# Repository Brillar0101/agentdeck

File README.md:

<div align="center">

# AgentDeck

**AgentDeck is an open-source desk macropad for supervising AI coding agents.**

</div>

_AgentDeck is optimized for people running several coding agents at once who
want glanceable status and one-hand control. It is a desk device, not a
portable one: USB-C only, no battery, no radio._

- [Design notes](v1/DESIGN.md)
- [Changelog](CHANGELOG.md)
- [Licensing](LICENSING.md)

Six agent keys light up with each agent's live state (idle, thinking, working,
blocked, done). Press one to focus that session. The command keys accept or
reject work, the dial scrubs and confirms, and the joystick navigates. A host
bridge maps Claude Code hooks to the key colours, so the board answers "which
of my sessions needs me?" without alt-tabbing.

> **This is a Codex Micro-inspired project.** The concept follows OpenAI and
> Work Louder's Codex Micro, and the control layout deliberately echoes it. It
> is an independent build, not affiliated with, endorsed by, or produced with
> OpenAI, Work Louder, or Anthropic. The board, firmware and enclosure are
> original work; no Codex Micro files were used. Some material in this
> repository (vendor footprints, datasheets, reference photographs, third-party
> cap and knob models) is not ours to license. See [LICENSING.md](LICENSING.md).

## Renders

| | |
|---|---|
|  |  |
|  |  |

## Changelog

Hardware revisions are tracked in the [changelog](CHANGELOG.md). Because the
board is text-based KiCad, every fabricated revision maps to a tagged commit,
and a physical board can be traced back to the exact design it was made from.

## Versions

| Version | What it is | Where |
|---|---|---|
| **V1** (this release) | 95 x 95 mm 4-layer RP2040 board, 13 keys, JLCPCB PCBA | `v1/hardware/` |

What comes next (v1.0 bring-up, the v1.1 depth release, and what is
deliberately parked) is in the [roadmap](docs/ROADMAP.md).

## Status

| Part | State |
|---|---|
| Schematic + PCB | Complete. 4 layers, fully routed, 0 DRC errors, 0 ERC errors |
| Firmware | Written (CircuitPython, plus an Arduino/C++ port), untested on hardware |
| Host bridge | Written. Maps Claude Code hooks to agent-key colours |
| Enclosure | Modelled and fit-checked in Blender, STLs exported, not yet printed |
| Fab package | Gerbers, BOM and CPL generated for JLCPCB |

Nothing has been manufactured yet, so none of it is hardware-verified.

## Packages

The repository is organized by discipline. Each directory is self-contained
and has its own README where the workflow needs explaining.

| Directory | Contents |
|---|---|
| `v1/hardware/` | KiCad 10 project: `AgentDeck.kicad_pcb`, `AgentDeck.kicad_sch`, footprint / symbol / 3D libraries |
| `v1/enclosure/` | Blender assembly (`AgentDeck-v2-assembled.blend`), the parametric case generator (`src/generate_case.py`), printable STLs, keycap icon art |
| `v1/firmware/` | CircuitPython firmware (`boot.py`, `code.py`) and the Arduino port |
| `v1/host/` | `agentdeck_bridge.py`, the Claude Code hook bridge |
| `v1/fab/` | Gerbers, drill files, BOM and CPL for JLCPCB |
| `docs/` | design notes, datasheets, reference material, renders in `docs/img/` |
| `LICENSES/` | full licence texts |

## Hardware

The board is a 95 x 95 mm 4-layer PCB, drawn in KiCad 10.

- 13 Kailh Choc hot-swap keys on an 18.7 x 19.3 mm grid, each with a
  reverse-mount SK6812MINI-E RGB LED shining up through the cap
- EC11 rotary encoder (top left) and Alps SKQUCAA010 5-way joystick (top right)
- RP2040 with W25Q128 16 MB flash, USB-C, BOOT button, SWD pads
- Everything is wired directly to GPIO. There is no key matrix, so there is
  no ghosting to debounce around
- All SMD parts sit on the back of the board and hang down into the case
  tray; only the switches, encoder and joystick face up

Keycaps carry simple engraved-style icons (dice for the six agent keys,
thumbs up and down for accept and reject) rendered from
[Lucide](https://lucide.dev) glyphs. The encoder and joystick caps are white.

## Enclosure

Two printed parts plus four printed cover caps. The PCB drops into the bottom
tray component-side down, the lid closes over it, and four screws clamp the
stack into brass inserts.

| Feature | Spec |
|---|---|
| Screws | M2.5 x 8 mm button head (ISO 7380), head 4.7 x 1.3 mm |
| Lid | 5.2 mm counterbore, 2.5 mm deep, over a 2.9 mm shaft hole |
| Inserts | M2.5 brass heat-set, 4.0 mm OD x 5.0 mm, melted into a 3.6 mm boss bore |
| Cover caps | printed 5.0 x 1.2 mm plugs that hide the screw heads |
| Fit | 0.4 mm pocket clearance around the board (a deliberately loose fit) |
| USB | side port through the tray wall, sized for the plug plus a slim overmould |
| Walls | 2.6 mm, with a 0.6 mm bevel on exposed edges |

Print `v1/enclosure/case-bottom.stl`, `v1/enclosure/case-top-lid.stl`, and four of
`v1/enclosure/case-cover-plug.stl`. The case is generated, not sculpted: edit the
parameters in `v1/enclosure/src/generate_case.py` and re-run it to get new STLs.

## Firmware

Copy `v1/firmware/boot.py` and `code.py` onto a CIRCUITPY drive running
CircuitPython 9.x, with `adafruit_hid` and `neopixel` in `lib/`. An Arduino
port with identical behaviour lives in `v1/firmware/arduino/` if you prefer a
compiled build.

The command keys send Ctrl+Alt chords, the dial sets reasoning effort, and the
joystick navigates. `v1/firmware/README.md` has the full control table, colour
legend, pin map, and the three constants to confirm on first hardware.

## Development

- **Board edits**: open `v1/hardware/AgentDeck.kicad_pcb` in KiCad 10. After
  copper changes, refill zones before running DRC, then regenerate `v1/fab/`
  with `kicad-cli`.
- **Case edits**: run `v1/enclosure/src/generate_case.py` in Blender to rebuild
  the STLs from parameters.
- **Renders**: the assembly lives in `v1/enclosure/AgentDeck-v2-assembled.blend`;
  reference renders are committed under `docs/img/`.
- Derived files (board 3D exports, `.dsn`/`.ses` routing intermediates,
  autorouter logs) are gitignored and regenerate from the board.

## Licence

Multi-licensed, as is normal for open hardware. See [LICENSING.md](LICENSING.md).

| What | Licence |
|---|---|
| Software (`v1/firmware/`, `v1/host/`) | [MIT](LICENSES/MIT.txt) |
| Hardware (board, enclosure, fab files) | [CERN-OHL-S v2](LICENSES/CERN-OHL-S-v2.txt) |
| Documentation | [CC-BY-4.0](LICENSES/CC-BY-4.0.txt) |

Vendor footprints, datasheets and reference images keep their original terms.
Keycap icons are from [Lucide](https://lucide.dev) (ISC).

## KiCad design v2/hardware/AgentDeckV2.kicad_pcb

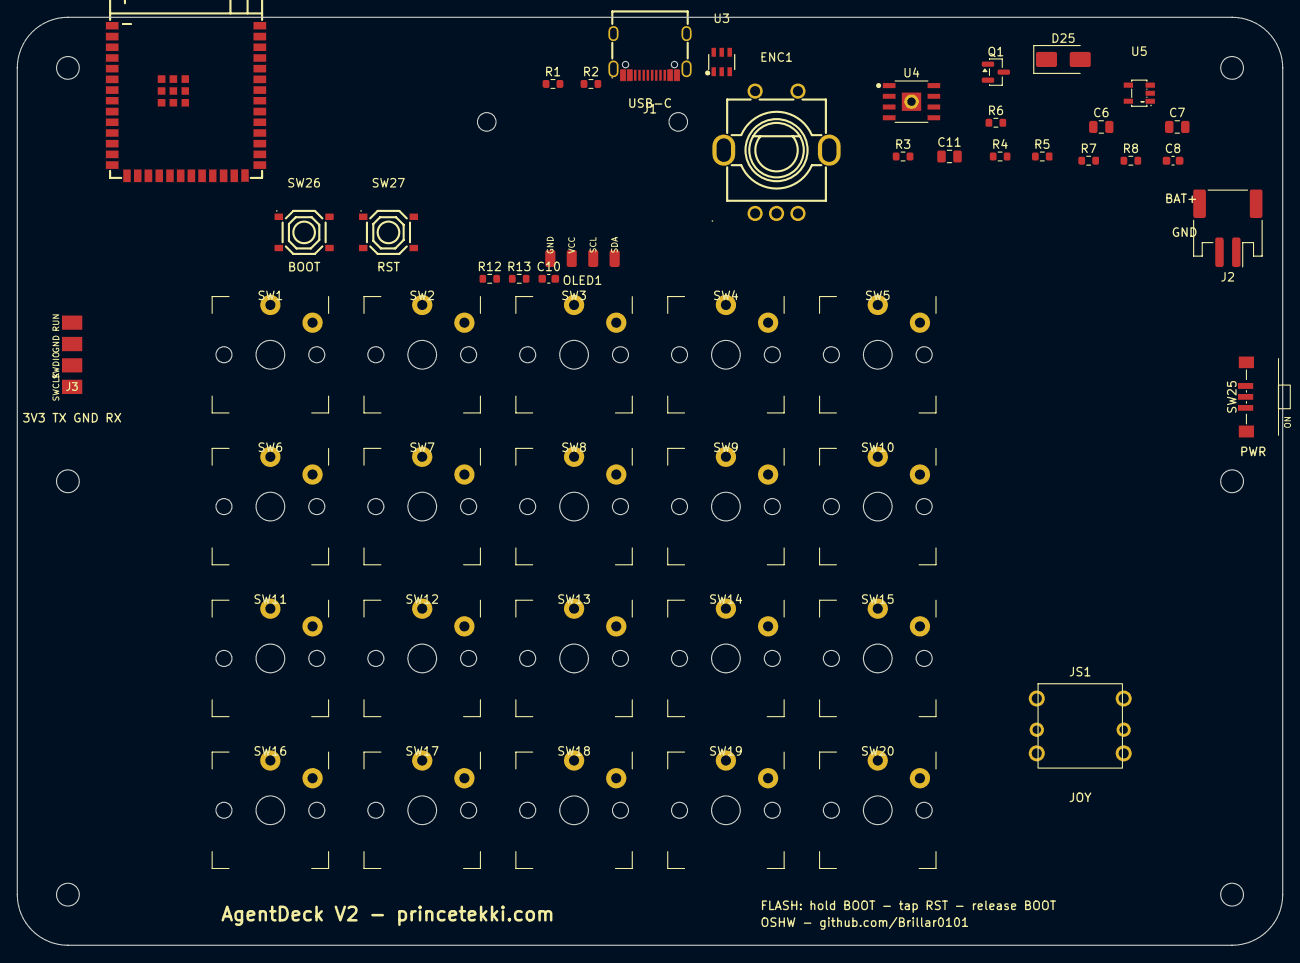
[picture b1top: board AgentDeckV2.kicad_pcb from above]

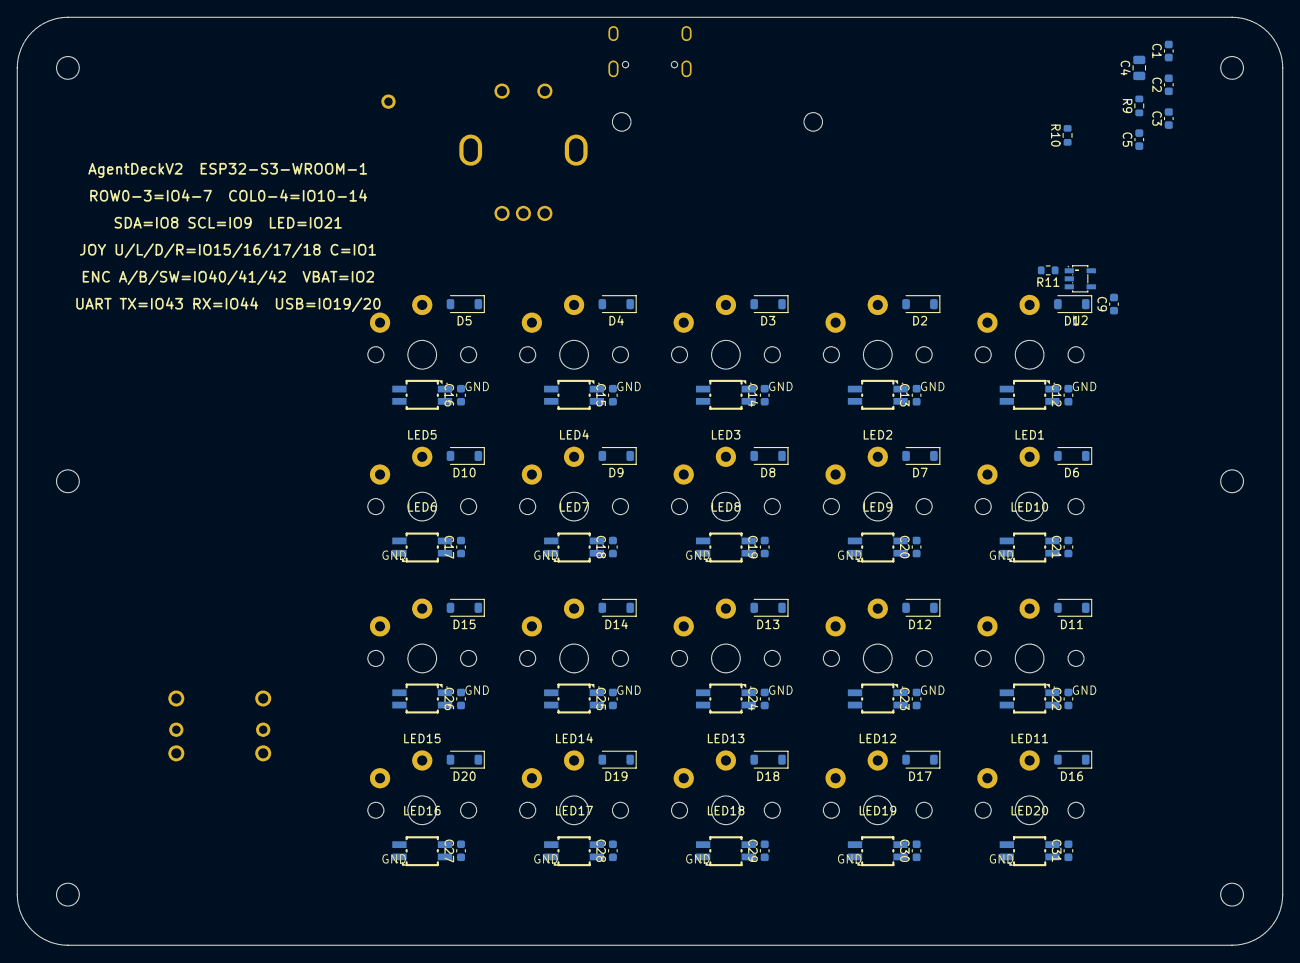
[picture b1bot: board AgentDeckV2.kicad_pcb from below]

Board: 2 copper layers, 150.0 x 110.0 mm, 126 parts (70 on the bottom side), 81 nets, no tracks yet.

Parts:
C1, C2, C3, C5, C8, C9, C10, C12, C13, C14, C15, C16, C17, C18, C19, C20, C21, C22, C23, C24, C25, C26, C27, C28, C29, C30, C31: C_0603_1608Metric
C4, C6, C7, C11: C_0805_2012Metric
D1, D2, D3, D4, D5, D6, D7, D8, D9, D10, D11, D12, D13, D14, D15, D16, D17, D18, D19, D20: D_SOD-123
D25: D_SMA
ENC1: SW-TH_EC11E1820402
J1: USB-C_SMD-TYPE-C-31-M-12_1
J2: JST_PH_S2B-PH-SM4-TB_1x02-1MP_P2.00mm_Horizontal
J3: SWD; ProgPads_1x4
JS1: SKQUCAA010
LED1, LED2, LED3, LED4, LED5, LED6, LED7, LED8, LED9, LED10, LED11, LED12, LED13, LED14, LED15, LED16, LED17, LED18, LED19, LED20: LED-SMD_4P-L3.2-W2.8-LS5.9_SK6812MINI-E
MH1, MH2, MH3, MH4, MH5, MH6: M2.5; MountingHole_M2_5
OLED1: OLED_HS96L03
Q1: SOT-23
R1, R2, R3, R4, R5, R6, R7, R8, R9, R10, R11, R12, R13: R_0603_1608Metric
SW1, SW2, SW3, SW4, SW5, SW6, SW7, SW8, SW9, SW10, SW11, SW12, SW13, SW14, SW15, SW16, SW17, SW18, SW19, SW20: ChocV1_Direct
SW25: MSK12C02
SW26, SW27: SW-SMD_4P-L5.1-W5.1-P3.70-LS6.5-TL_H1.5
U1: WIRELM-SMD_ESP32-S3-WROOM-1
U2, U5: SOT-23-5_L3.0-W1.7-P0.95-LS2.8-BR
U3: SOT-23-6_L2.9-W1.6-P0.95-LS2.8-BL
U4: ESOP-8_TP4056

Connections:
+3V3: C1.1, C2.1, C3.1, C4.1, C7.1, C10.1, J3.1, OLED1.2, R9.1, R10.1, R12.1, R13.1, U1.2, U5.5
BAT+: J2.1, Q1.3, R7.1, U4.5
CC1: J1.A5, R1.1
CC2: J1.B5, R2.1
CHRG: R4.1, U4.7
CHRG_SNS: R4.2, U1.24
COL0: SW1.1, SW6.1, SW11.1, SW16.1, U1.18
COL1: SW2.1, SW7.1, SW12.1, SW17.1, U1.19
COL2: SW3.1, SW8.1, SW13.1, SW18.1, U1.20
COL3: SW4.1, SW9.1, SW14.1, SW19.1, U1.21
COL4: SW5.1, SW10.1, SW15.1, SW20.1, U1.22
EN: C5.1, R9.2, SW27.1, SW27.3, U1.3
ENC_A: ENC1.A, U1.33
ENC_B: ENC1.B, U1.34
ENC_SW: ENC1.D, U1.35
GND: C1.2, C2.2, C3.2, C4.2, C5.2, C6.2, C7.2, C8.2, C9.2, C10.2, C11.2, C12.2, C13.2, C14.2, C15.2, C16.2, C17.2, C18.2, C19.2, C20.2, C21.2, C22.2, C23.2, C24.2, C25.2, C26.2, C27.2, C28.2, C29.2, C30.2, C31.2, ENC1.C, ENC1.E, ENC1.F, ENC1.G, J1.1, J1.2, J1.3, J1.4, J1.A1B12, J1.B1A12, J2.2, J3.3, JS1.4, LED1.1, LED2.1, LED3.1, LED4.1, LED5.1, LED6.1, LED7.1, LED8.1, LED9.1, LED10.1, LED11.1, LED12.1, LED13.1, LED14.1, LED15.1, LED16.1, LED17.1, LED18.1, LED19.1, LED20.1, OLED1.1, R1.2, R2.2, R3.2, R6.2, R8.2, SW26.2, SW26.4, SW27.2, SW27.4, U1.1, U1.40, U1.41, U2.1, U2.3, U3.2, U4.1, U4.3, U5.2
IO0: R10.2, SW26.1, SW26.3, U1.27
JOY_CTR: JS1.6, U1.39
JOY_DOWN: JS1.3, U1.10
JOY_LEFT: JS1.2, U1.9
JOY_RIGHT: JS1.5, U1.11
JOY_UP: JS1.1, U1.8
KD1: D1.2, SW1.2
KD2: D2.2, SW2.2
KD3: D3.2, SW3.2
KD4: D4.2, SW4.2
KD5: D5.2, SW5.2
KD6: D6.2, SW6.2
KD7: D7.2, SW7.2
KD8: D8.2, SW8.2
KD9: D9.2, SW9.2
KD10: D10.2, SW10.2
KD11: D11.2, SW11.2
KD12: D12.2, SW12.2
KD13: D13.2, SW13.2
KD14: D14.2, SW14.2
KD15: D15.2, SW15.2
KD16: D16.2, SW16.2
KD17: D17.2, SW17.2
KD18: D18.2, SW18.2
KD19: D19.2, SW19.2
KD20: D20.2, SW20.2
LED_D1: LED1.2, R11.2
LED_D2: LED1.4, LED2.2
LED_D3: LED2.4, LED3.2
LED_D4: LED3.4, LED4.2
LED_D5: LED4.4, LED5.2
LED_D6: LED5.4, LED6.2
LED_D7: LED6.4, LED7.2
LED_D8: LED7.4, LED8.2
LED_D9: LED8.4, LED9.2
LED_D10: LED9.4, LED10.2
LED_D11: LED10.4, LED11.2
LED_D12: LED11.4, LED12.2
LED_D13: LED12.4, LED13.2
LED_D14: LED13.4, LED14.2
LED_D15: LED14.4, LED15.2
LED_D16: LED15.4, LED16.2
LED_D17: LED16.4, LED17.2
LED_D18: LED17.4, LED18.2
LED_D19: LED18.4, LED19.2
LED_D20: LED19.4, LED20.2
LED_DATA: U1.23, U2.2
LED_DATA_BUF: R11.1, U2.4
PROG: R3.1, U4.2
ROW0: D1.1, D2.1, D3.1, D4.1, D5.1, U1.4
ROW1: D6.1, D7.1, D8.1, D9.1, D10.1, U1.5
ROW2: D11.1, D12.1, D13.1, D14.1, D15.1, U1.6
ROW3: D16.1, D17.1, D18.1, D19.1, D20.1, U1.7
RXD: J3.4, U1.36
SCL: OLED1.3, R13.2, U1.17
SDA: OLED1.4, R12.2, U1.12
STDBY: R5.1, U4.6
STDBY_SNS: R5.2, U1.25
TXD: J3.2, U1.37
USB_DM: J1.A7, J1.B7, U1.13, U3.1, U3.6
USB_DP: J1.A6, J1.B6, U1.14, U3.3, U3.4
VBAT_SNS: C8.1, R7.2, R8.1, U1.38
VBUS: C11.1, D25.2, J1.A4B9, J1.B4A9, Q1.1, R6.1, U3.5, U4.4, U4.8
VSYS: D25.1, Q1.2, SW25.2
VSYS_SW: C6.1, C9.1, C12.1, C13.1, C14.1, C15.1, C16.1, C17.1, C18.1, C19.1, C20.1, C21.1, C22.1, C23.1, C24.1, C25.1, C26.1, C27.1, C28.1, C29.1, C30.1, C31.1, LED1.3, LED2.3, LED3.3, LED4.3, LED5.3, LED6.3, LED7.3, LED8.3, LED9.3, LED10.3, LED11.3, LED12.3, LED13.3, LED14.3, LED15.3, LED16.3, LED17.3, LED18.3, LED19.3, LED20.3, SW25.1, U2.5, U5.1, U5.3

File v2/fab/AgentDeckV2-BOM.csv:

Designators,Qty,Value,Footprint,LCSC,Notes
"C1,C12,C13,C14,C15,C16,C17,C18,C19,C2,C20,C21,C22,C23,C24,C25,C26,C27,C28,C29,C3,C30,C31,C5,C9",25,100nF,C_0603_1608Metric,C14663,
C4,1,10uF,C_0805_2012Metric,C19702,
"C6,C7",2,1uF,C_0805_2012Metric,C128624,
"D1,D10,D11,D12,D13,D14,D15,D16,D17,D18,D19,D2,D20,D21,D22,D23,D24,D25,D3,D4,D5,D6,D7,D8,D9",25,1N4148W,D_SOD-123,C81598,
ENC1,1,EC11,SW-TH_EC11E1820402,C361165,
J1,1,TYPE-C-31-M-12,USB-C_SMD-TYPE-C-31-M-12_1,C165948,
J3,1,ProgPads 3V3/TX/GND/RX,ProgPads_1x4,,not an LCSC line - see v2/PARTS.yaml
JS1,1,SKQUCAA010,SKQUCAA010,,not an LCSC line - see v2/PARTS.yaml
"LED1,LED10,LED11,LED12,LED13,LED14,LED15,LED16,LED17,LED18,LED19,LED2,LED20,LED3,LED4,LED5,LED6,LED7,LED8,LED9",20,SK6812MINI-E,LED-SMD_4P-L3.2-W2.8-LS5.9_SK6812MINI-E,C5149201,
"R1,R2",2,5.1k,R_0603_1608Metric,C23186,
R11,1,330R,R_0603_1608Metric,C23138,
"R10,R9",2,10k,R_0603_1608Metric,C25804,
"SW1,SW10,SW11,SW12,SW13,SW14,SW15,SW16,SW17,SW18,SW19,SW2,SW20,SW3,SW4,SW5,SW6,SW7,SW8,SW9",20,ChocV1,CONN-SMD_HOTPLUGPAKAGE__C9900010116,,not an LCSC line - see v2/PARTS.yaml
"SW26,SW27",2,SW_PUSH,SW-SMD_4P-L5.1-W5.1-P3.70-LS6.5-TL_H1.5,C318884,
U1,1,ESP32-S3-WROOM-1-N8R2,WIRELM-SMD_ESP32-S3-WROOM-1,C2913204,
U2,1,SN74AHCT1G125,SOT-23-5_L3.0-W1.7-P0.95-LS2.8-BR,C7484,
U3,1,USBLC6-2SC6,SOT-23-6_L2.9-W1.6-P0.95-LS2.8-BL,C7519,
U5,1,ME6211C33,SOT-23-5_L3.0-W1.7-P0.95-LS2.8-BR,C82942,

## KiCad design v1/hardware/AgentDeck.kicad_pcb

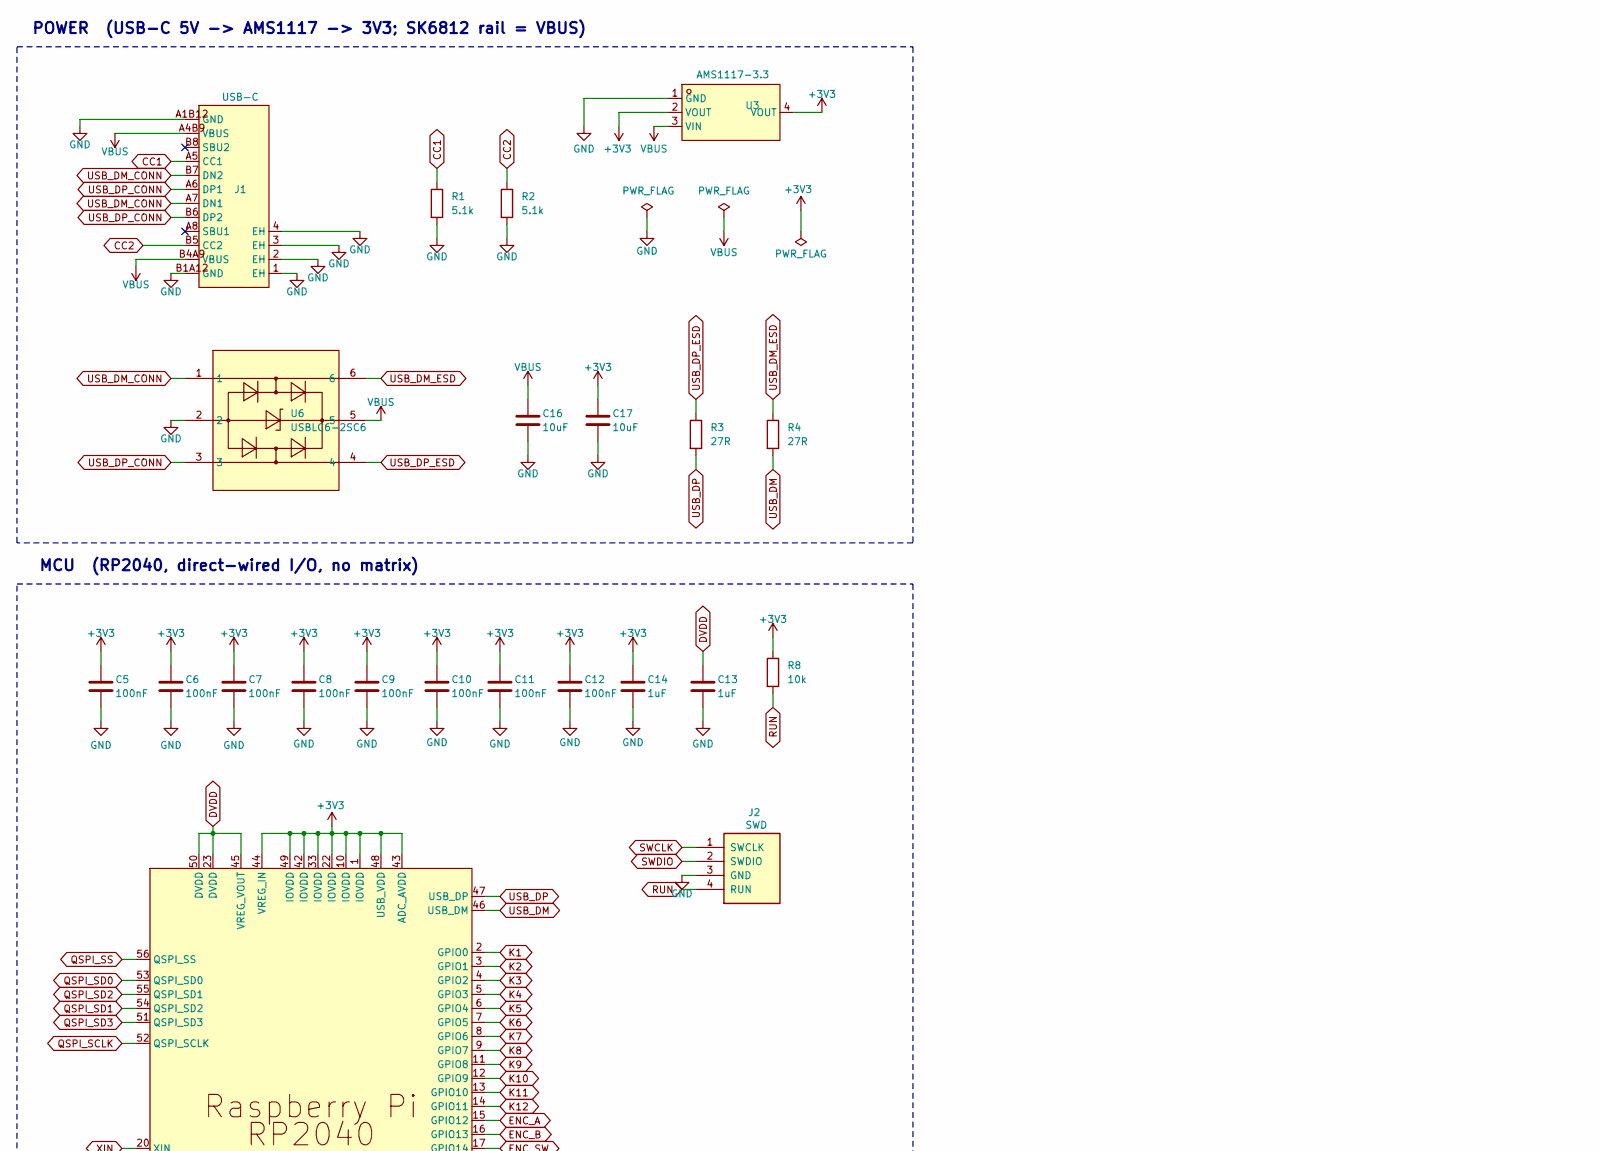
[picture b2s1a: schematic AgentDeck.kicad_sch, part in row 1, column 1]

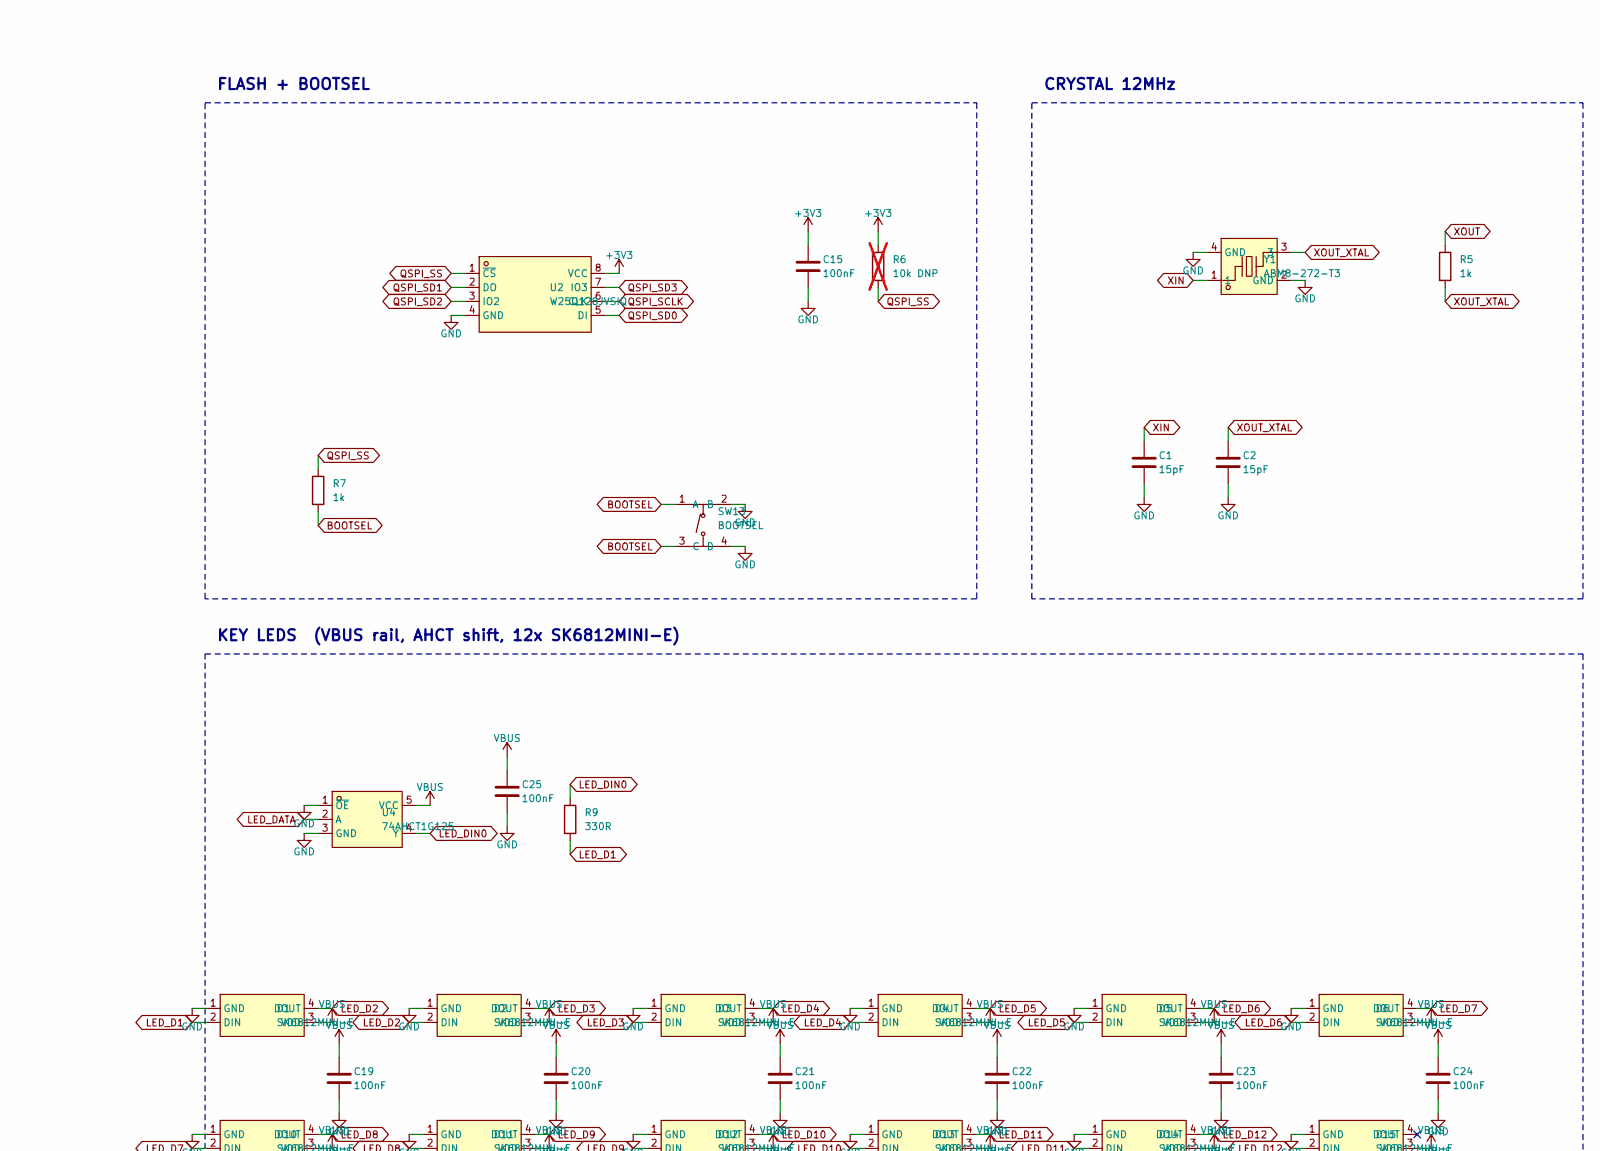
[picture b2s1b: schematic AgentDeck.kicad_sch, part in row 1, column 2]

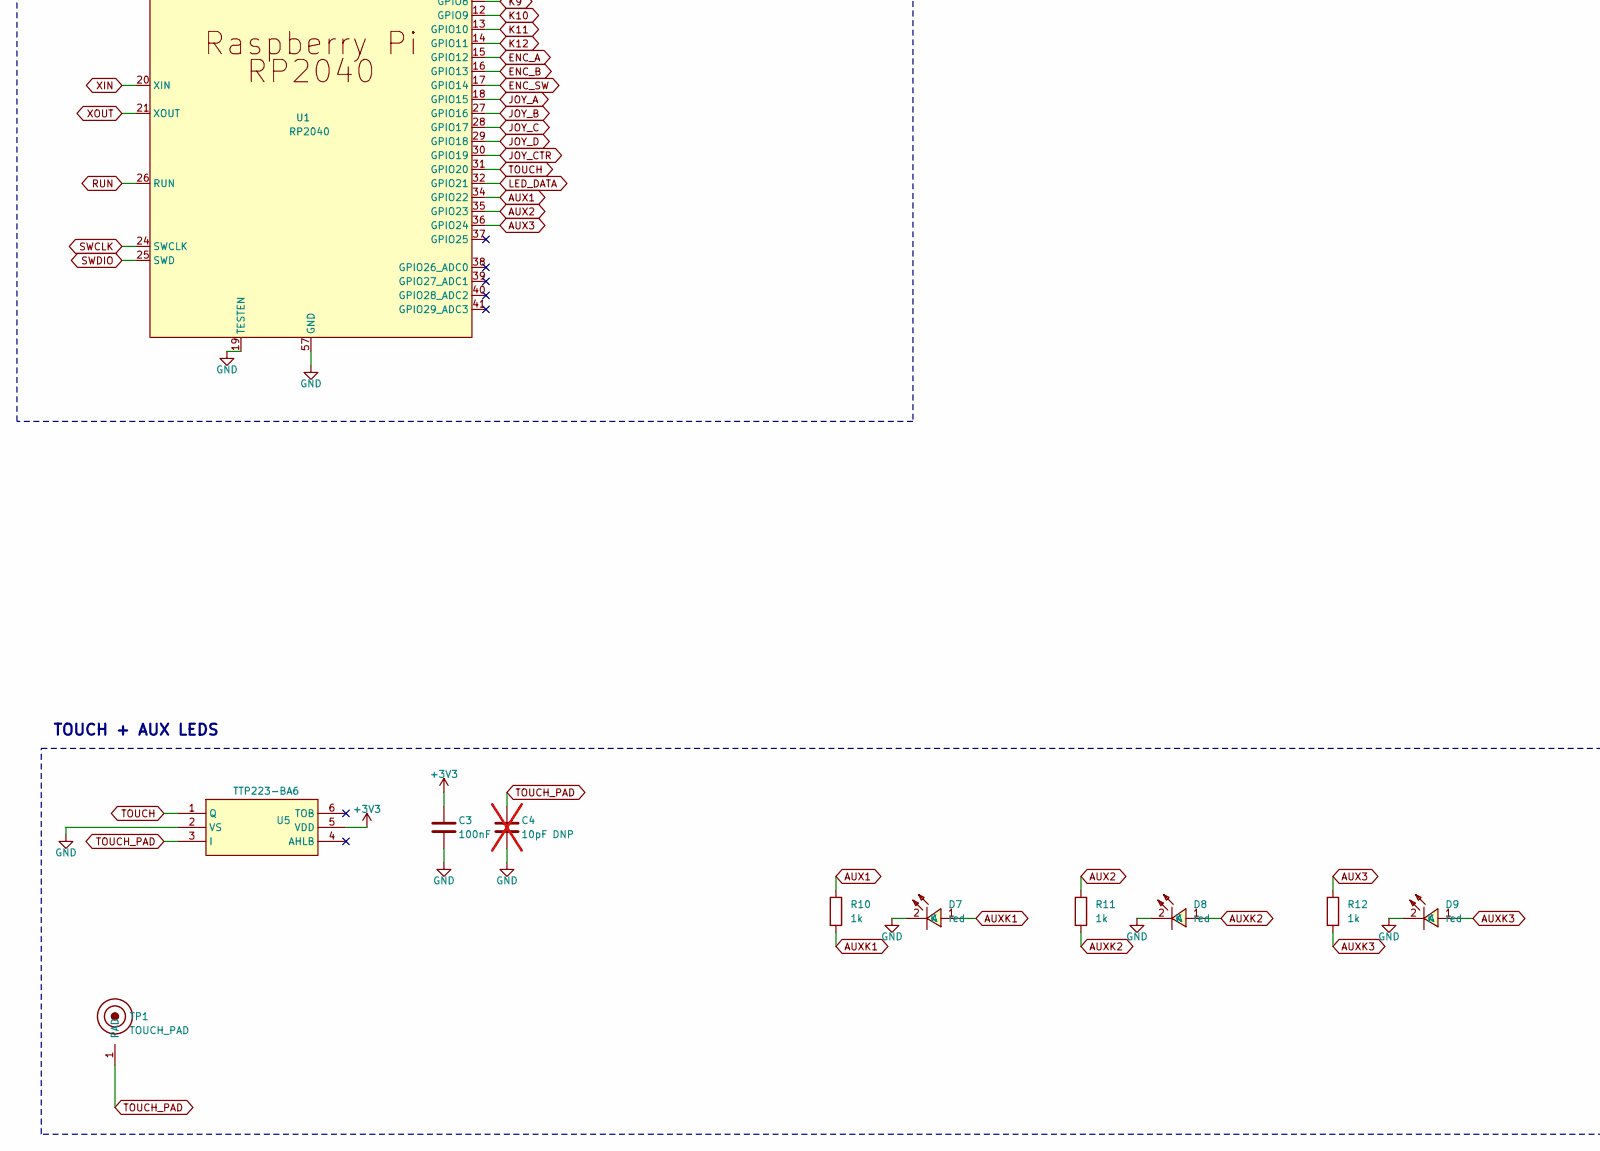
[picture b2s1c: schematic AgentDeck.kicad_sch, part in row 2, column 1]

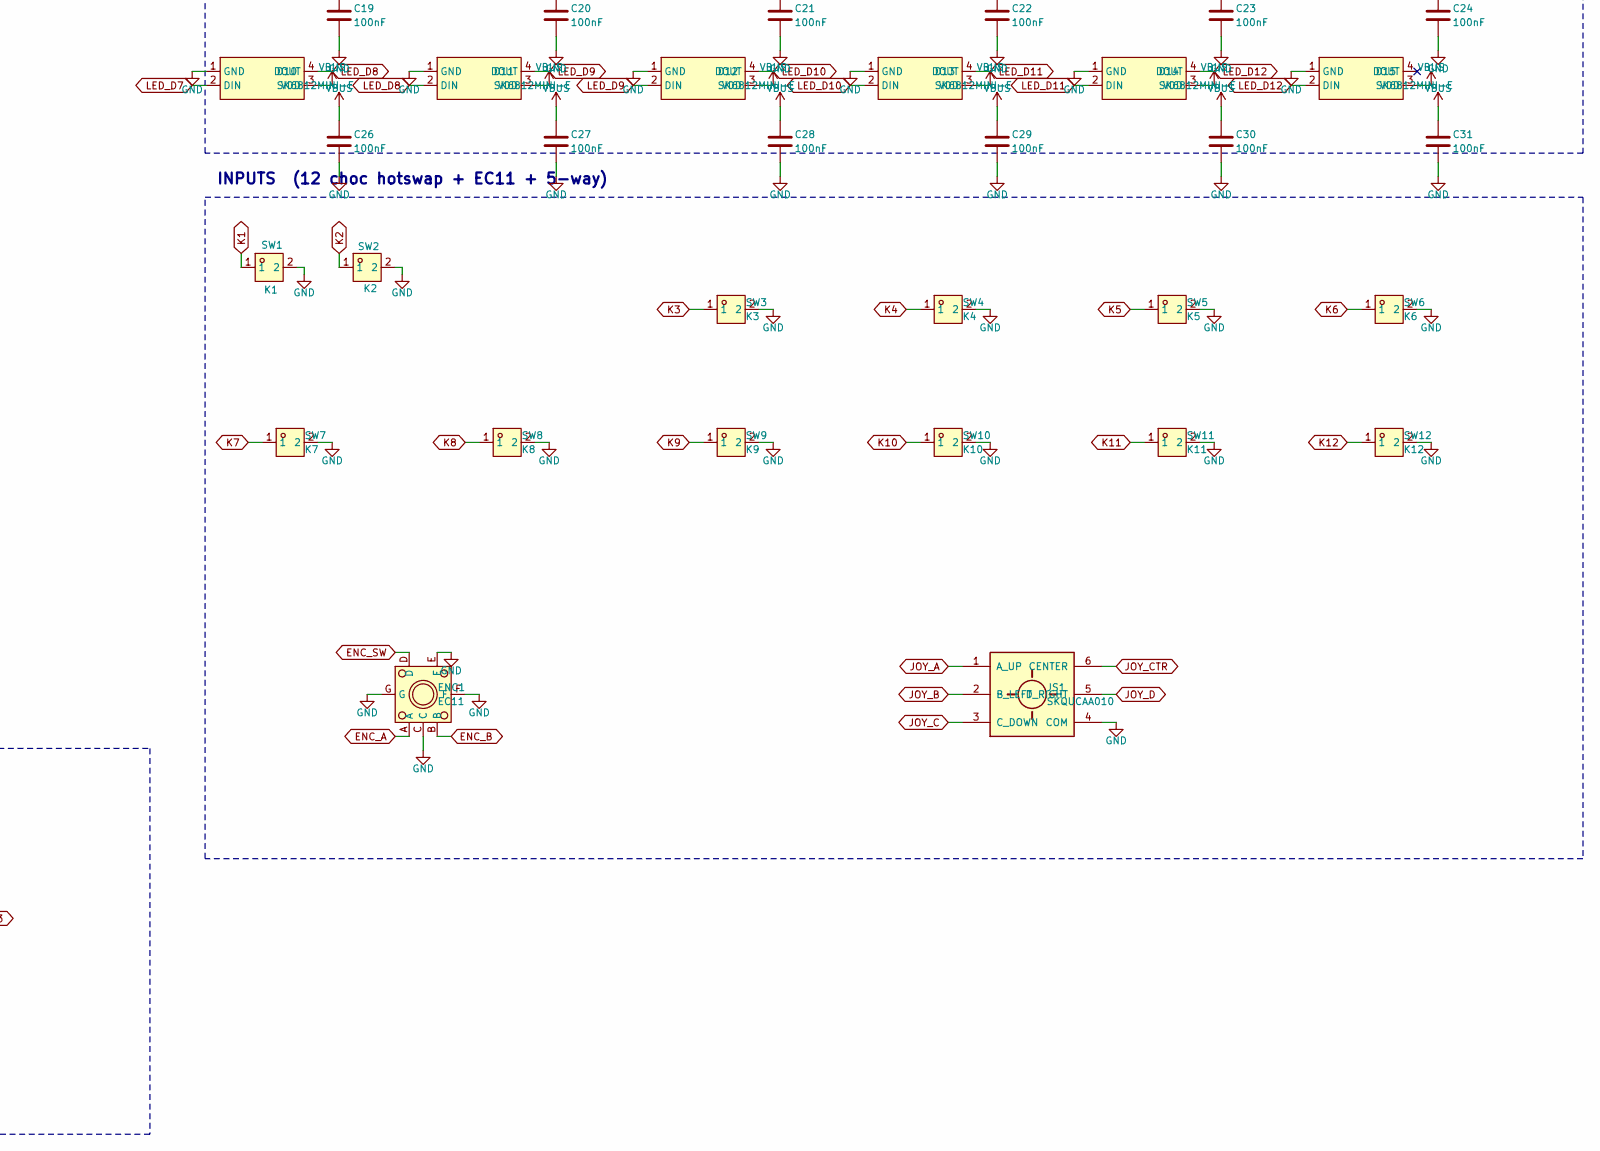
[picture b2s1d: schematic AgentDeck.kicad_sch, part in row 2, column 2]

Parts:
C1, C2: 15pF; C_0603_1608Metric
C3, C5, C6, C7, C8, C9, C10, C11, C12, C15, C19, C20, C21, C22, C23, C24, C25, C26, C27, C28, C29, C30, C31: 100nF; C_0603_1608Metric
C4: 10pF DNP; C_0603_1608Metric; not fitted
C13, C14: 1uF; C_0603_1608Metric
C16, C17: 10uF; C_0603_1608Metric
D1, D2, D3, D4, D5, D6, D10, D11, D12, D13, D14, D15: SK6812MINI-E; LED-SMD_4P-L3.2-W2.8-LS5.9_SK6812MINI-E
D7, D8, D9: red; LED-SMD_L1.6-W0.8-R-RD
ENC1: EC11; SW-TH_EC11E1820402
J1: USB-C; USB-C_SMD-TYPE-C-31-M-12_1
J2: SWD; ProgPads_1x4
JS1: SKQUCAA010
R1, R2: 5.1k; R_0603_1608Metric
R3, R4: 27R; R_0603_1608Metric
R5, R7, R10, R11, R12: 1k; R_0603_1608Metric
R6: 10k DNP; R_0603_1608Metric; not fitted
R8: 10k; R_0603_1608Metric
R9: 330R; R_0603_1608Metric
SW1: K1; CONN-SMD_HOTPLUGPAKAGE__C9900010116
SW2: K2; CONN-SMD_HOTPLUGPAKAGE__C9900010116
SW3: K3; CONN-SMD_HOTPLUGPAKAGE__C9900010116
SW4: K4; CONN-SMD_HOTPLUGPAKAGE__C9900010116
SW5: K5; CONN-SMD_HOTPLUGPAKAGE__C9900010116
SW6: K6; CONN-SMD_HOTPLUGPAKAGE__C9900010116
SW7: K7; CONN-SMD_HOTPLUGPAKAGE__C9900010116
SW8: K8; CONN-SMD_HOTPLUGPAKAGE__C9900010116
SW9: K9; CONN-SMD_HOTPLUGPAKAGE__C9900010116
SW10: K10; CONN-SMD_HOTPLUGPAKAGE__C9900010116
SW11: K11; CONN-SMD_HOTPLUGPAKAGE__C9900010116
SW12: K12; CONN-SMD_HOTPLUGPAKAGE__C9900010116
SW13: BOOTSEL; SW-SMD_4P-L5.1-W5.1-P3.70-LS6.5-TL_H1.5
TP1: TOUCH_PAD; TouchPad_D12
U1: RP2040; LQFN-56_L7.0-W7.0-P0.4-EP
U2: W25Q128JVSIQ; SOIC-8_L5.3-W5.3-P1.27-LS8.0-BL
U3: AMS1117-3.3; SOT-223-3_L6.5-W3.4-P2.30-LS7.0-BR
U4: 74AHCT1G125; SOT-23-5_L3.0-W1.7-P0.95-LS2.8-BR
U5: TTP223-BA6; SOT-23-6_L2.9-W1.6-P0.95-LS2.8-BL
U6: USBLC6-2SC6; SOT-23-6_L2.9-W1.6-P0.95-LS2.8-BL
Y1: ABM8-272-T3; CRYSTAL-SMD_4P-L3.2-W2.5-BL

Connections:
+3V3: C3.1, C5.1, C6.1, C7.1, C8.1, C9.1, C10.1, C11.1, C12.1, C14.1, C15.1, C17.1, R6.1, R8.1, U1.1 (IOVDD), U1.10 (IOVDD), U1.22 (IOVDD), U1.33 (IOVDD), U1.42 (IOVDD), U1.43 (ADC_AVDD), U1.44 (VREG_IN), U1.48 (USB_VDD), U1.49 (IOVDD), U2.8 (VCC), U3.2 (VOUT), U3.4 (VOUT), U5.5 (VDD)
AUX1: R10.1, U1.34 (GPIO22)
AUX2: R11.1, U1.35 (GPIO23)
AUX3: R12.1, U1.36 (GPIO24)
AUXK1: D7.1 (A), R10.2
AUXK2: D8.1 (A), R11.2
AUXK3: D9.1 (A), R12.2
BOOTSEL: R7.2, SW13.1 (A), SW13.3 (C)
CC1: J1.A5 (CC1), R1.1
CC2: J1.B5 (CC2), R2.1
DVDD: C13.1, U1.23 (DVDD), U1.45 (VREG_VOUT), U1.50 (DVDD)
ENC_A: ENC1.A, U1.15 (GPIO12)
ENC_B: ENC1.B, U1.16 (GPIO13)
ENC_SW: ENC1.D, U1.17 (GPIO14)
GND: C1.2, C2.2, C3.2, C4.2, C5.2, C6.2, C7.2, C8.2, C9.2, C10.2, C11.2, C12.2, C13.2, C14.2, C15.2, C16.2, C17.2, C19.2, C20.2, C21.2, C22.2, C23.2, C24.2, C25.2, C26.2, C27.2, C28.2, C29.2, C30.2, C31.2, D1.1 (GND), D2.1 (GND), D3.1 (GND), D4.1 (GND), D5.1 (GND), D6.1 (GND), D7.2 (K), D8.2 (K), D9.2 (K), D10.1 (GND), D11.1 (GND), D12.1 (GND), D13.1 (GND), D14.1 (GND), D15.1 (GND), ENC1.C, ENC1.E, ENC1.F, ENC1.G, J1.1 (EH), J1.2 (EH), J1.3 (EH), J1.4 (EH), J1.A1B12 (GND), J1.B1A12 (GND), J2.3 (GND), JS1.4 (COM), R1.2, R2.2, SW1.2, SW2.2, SW3.2, SW4.2, SW5.2, SW6.2, SW7.2, SW8.2, SW9.2, SW10.2, SW11.2, SW12.2, SW13.2 (B), SW13.4 (D), U1.19 (TESTEN), U1.57 (GND), U2.4 (GND), U3.1 (GND), U4.1 (~OE), U4.3 (GND), U5.2 (VS), U6.2, Y1.2 (GND), Y1.4 (GND); also elsewhere on the board
JOY_A: JS1.1 (A_UP), U1.18 (GPIO15)
JOY_B: JS1.2 (B_LEFT), U1.27 (GPIO16)
JOY_C: JS1.3 (C_DOWN), U1.28 (GPIO17)
JOY_CTR: JS1.6 (CENTER), U1.30 (GPIO19)
JOY_D: JS1.5 (D_RIGHT), U1.29 (GPIO18)
K1: SW1.1, U1.2 (GPIO0)
K2: SW2.1, U1.3 (GPIO1)
K3: SW3.1, U1.4 (GPIO2)
K4: SW4.1, U1.5 (GPIO3)
K5: SW5.1, U1.6 (GPIO4)
K6: SW6.1, U1.7 (GPIO5)
K7: SW7.1, U1.8 (GPIO6)
K8: SW8.1, U1.9 (GPIO7)
K9: SW9.1, U1.11 (GPIO8)
K10: SW10.1, U1.12 (GPIO9)
K11: SW11.1, U1.13 (GPIO10)
K12: SW12.1, U1.14 (GPIO11)
LED_D1: D1.2 (DIN), R9.2
LED_D2: D1.4 (DOUT), D2.2 (DIN)
LED_D3: D2.4 (DOUT), D3.2 (DIN)
LED_D4: D3.4 (DOUT), D4.2 (DIN)
LED_D5: D4.4 (DOUT), D5.2 (DIN)
LED_D6: D5.4 (DOUT), D6.2 (DIN)
LED_D7: D6.4 (DOUT), D10.2 (DIN)
LED_D8: D10.4 (DOUT), D11.2 (DIN)
LED_D9: D11.4 (DOUT), D12.2 (DIN)
LED_D10: D12.4 (DOUT), D13.2 (DIN)
LED_D11: D13.4 (DOUT), D14.2 (DIN)
LED_D12: D14.4 (DOUT), D15.2 (DIN)
LED_D13: D15.4 (DOUT); also elsewhere on the board
LED_DATA: U1.32 (GPIO21), U4.2 (A)
LED_DIN0: R9.1, U4.4 (Y)
unnamed: C4.1, TP1.1, U5.3 (I)
QSPI_SCLK: U1.52 (QSPI_SCLK), U2.6 (CLK)
QSPI_SD0: U1.53 (QSPI_SD0), U2.5 (DI)
QSPI_SD1: U1.54 (QSPI_SD2), U2.2 (DO)
QSPI_SD2: U1.55 (QSPI_SD1), U2.3 (IO2)
QSPI_SD3: U1.51 (QSPI_SD3), U2.7 (IO3)
QSPI_SS: R6.2, R7.1, U1.56 (QSPI_SS), U2.1 (~CS)
RUN: J2.4 (RUN), R8.2, U1.26 (RUN)
SWCLK: J2.1 (SWCLK), U1.24 (SWCLK)
SWDIO: J2.2 (SWDIO), U1.25 (SWD)
TOUCH: U1.31 (GPIO20), U5.1 (Q); also elsewhere on the board
USB_DM: R4.2, U1.46 (USB_DM)
USB_DM_CONN: J1.A7 (DN1), J1.B7 (DN2), U6.1
USB_DM_ESD: R4.1, U6.6
USB_DP: R3.2, U1.47 (USB_DP)
USB_DP_CONN: J1.A6 (DP1), J1.B6 (DP2), U6.3
USB_DP_ESD: R3.1, U6.4
VBUS: C16.1, C19.1, C20.1, C21.1, C22.1, C23.1, C24.1, C25.1, C26.1, C27.1, C28.1, C29.1, C30.1, C31.1, D1.3 (VDD), D2.3 (VDD), D3.3 (VDD), D4.3 (VDD), D5.3 (VDD), D6.3 (VDD), D10.3 (VDD), D11.3 (VDD), D12.3 (VDD), D13.3 (VDD), D14.3 (VDD), D15.3 (VDD), J1.A4B9 (VBUS), J1.B4A9 (VBUS), U3.3 (VIN), U4.5 (VCC), U6.5; also elsewhere on the board
XIN: C1.1, U1.20 (XIN), Y1.1
XOUT: R5.1, U1.21 (XOUT)
XOUT_XTAL: C2.1, R5.2, Y1.3

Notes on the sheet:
POWER (USB-C 5V -> AMS1117 -> 3V3; SK6812 rail = VBUS)
CRYSTAL 12MHz
INPUTS (12 choc hotswap + EC11 + 5-way)
FLASH + BOOTSEL
TOUCH + AUX LEDS
MCU (RP2040, direct-wired I/O, no matrix)
KEY LEDS (VBUS rail, AHCT shift, 12x SK6812MINI-E)

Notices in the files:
v1/hardware/AgentDeck.kicad_pcb:
AgentDeck v1.0.0 · OSHW · CERN-OHL-S v2 · github.com/Brillar0101
